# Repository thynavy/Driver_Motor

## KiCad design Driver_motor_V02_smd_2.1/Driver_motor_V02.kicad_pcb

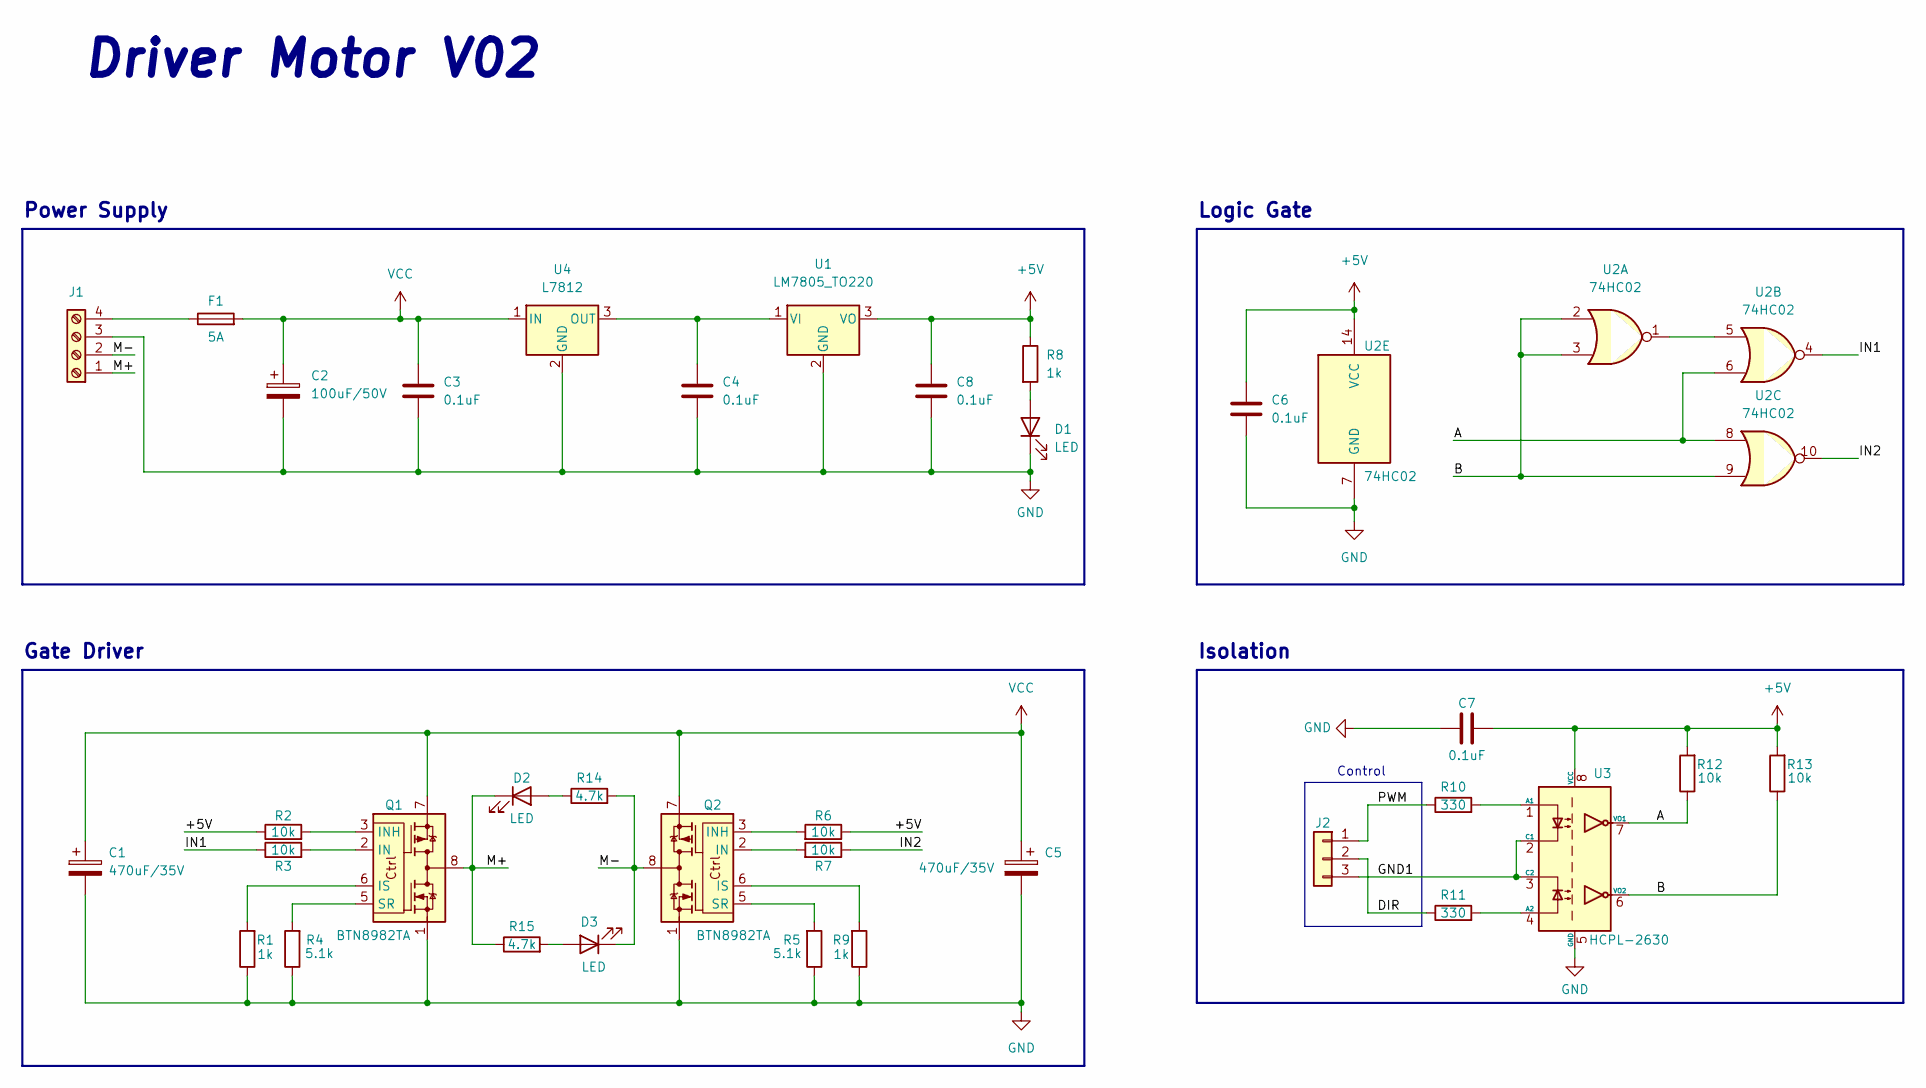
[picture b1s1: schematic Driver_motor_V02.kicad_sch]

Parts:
C1, C5: 470uF/35V; CP_Radial_D10.0mm_P5.00mm
C2: 100uF/50V; CP_Radial_D8.0mm_P3.80mm
C3, C4, C6, C7, C8: 0.1uF; C_0805_2012Metric
D1, D2, D3: LED; LED_0805_2012Metric
F1: 5A; Fuseholder_Cylinder-5x20mm_Schurter_0031_8201_Horizontal_Op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
J1: Screw_Terminal_01x04; KF7.62_2O
J2: Conn_01x03; JST_XH_B3B-XH-A_1x03_P2.50mm_Vertical
Q1, Q2: BTN8982TA; TO-263-7_TabPin8
R1, R8, R9: 1k; R_0805_2012Metric
R2, R3, R6, R7, R12, R13: 10k; R_0805_2012Metric
R4, R5: 5.1k; R_0805_2012Metric
R10, R11: 330; R_0805_2012Metric
R14, R15: 4.7k; R_0805_2012Metric
U1: LM7805_TO220; TO-252-2
U2: 74HC02; DIP-14_W7.62mm_Socket_LongPads
U3: HCPL-2630; DIP-8_W7.62mm_Socket_LongPads
U4: L7812; TO-252-2

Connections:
+5V: C6.1, C7.2, C8.1, R2.1, R6.1, R8.1, R12.2, R13.2, U1.3 (VO), U2.14 (VCC), U3.8 (VCC)
/A: R12.1, U2.6, U2.8, U3.7 (VO1)
/B: R13.1, U2.2, U2.3, U2.9, U3.6 (VO2)
/DIR: J2.2, R11.1
/GND1: J2.3, U3.2 (C1), U3.3 (C2)
/IN1: R3.1, U2.4
/IN2: R7.1, U2.10
/M+: D2.1 (K), J1.1, Q1.4, Q1.8, R15.1
/M-: D3.1 (K), J1.2, Q2.4, Q2.8, R14.2
/PWM: J2.1, R10.1
GND: C1.2, C2.2, C3.2, C4.2, C5.2, C6.2, C7.1, C8.2, D1.1 (K), J1.3, Q1.1, Q2.1, R1.1, R4.1, R5.1, R9.1, U1.2 (GND), U2.7 (GND), U3.5 (GND), U4.2 (GND)
unnamed: C4.1, U1.1 (VI), U4.3 (OUT)
unnamed: D1.2 (A), R8.2
unnamed: D2.2 (A), R14.1
unnamed: D3.2 (A), R15.2
unnamed: F1.1, J1.4
unnamed: Q1.2 (IN), R3.2
unnamed: Q1.3 (INH), R2.2
unnamed: Q1.5 (SR), R4.2
unnamed: Q1.6 (IS), R1.2
unnamed: Q2.2 (IN), R7.2
unnamed: Q2.3 (INH), R6.2
unnamed: Q2.5 (SR), R5.2
unnamed: Q2.6 (IS), R9.2
unnamed: R10.2, U3.1 (A1)
unnamed: R11.2, U3.4 (A2)
unnamed: U2.1, U2.5
VCC: C1.1, C2.1, C3.1, C5.1, F1.2, Q1.7, Q2.7, U4.1 (IN)

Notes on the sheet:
Driver Motor V02
Power Supply
Control
Gate Driver
Isolation
Logic Gate

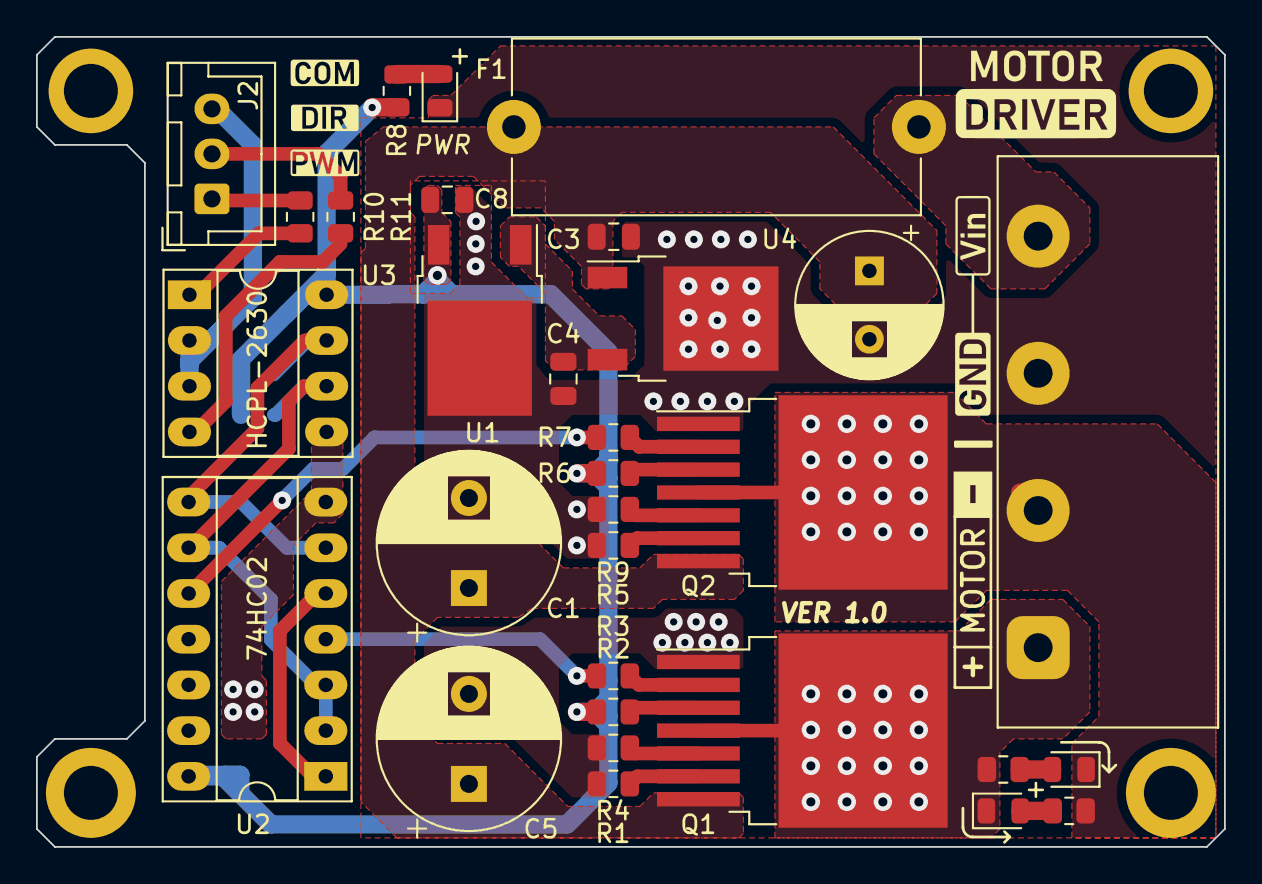
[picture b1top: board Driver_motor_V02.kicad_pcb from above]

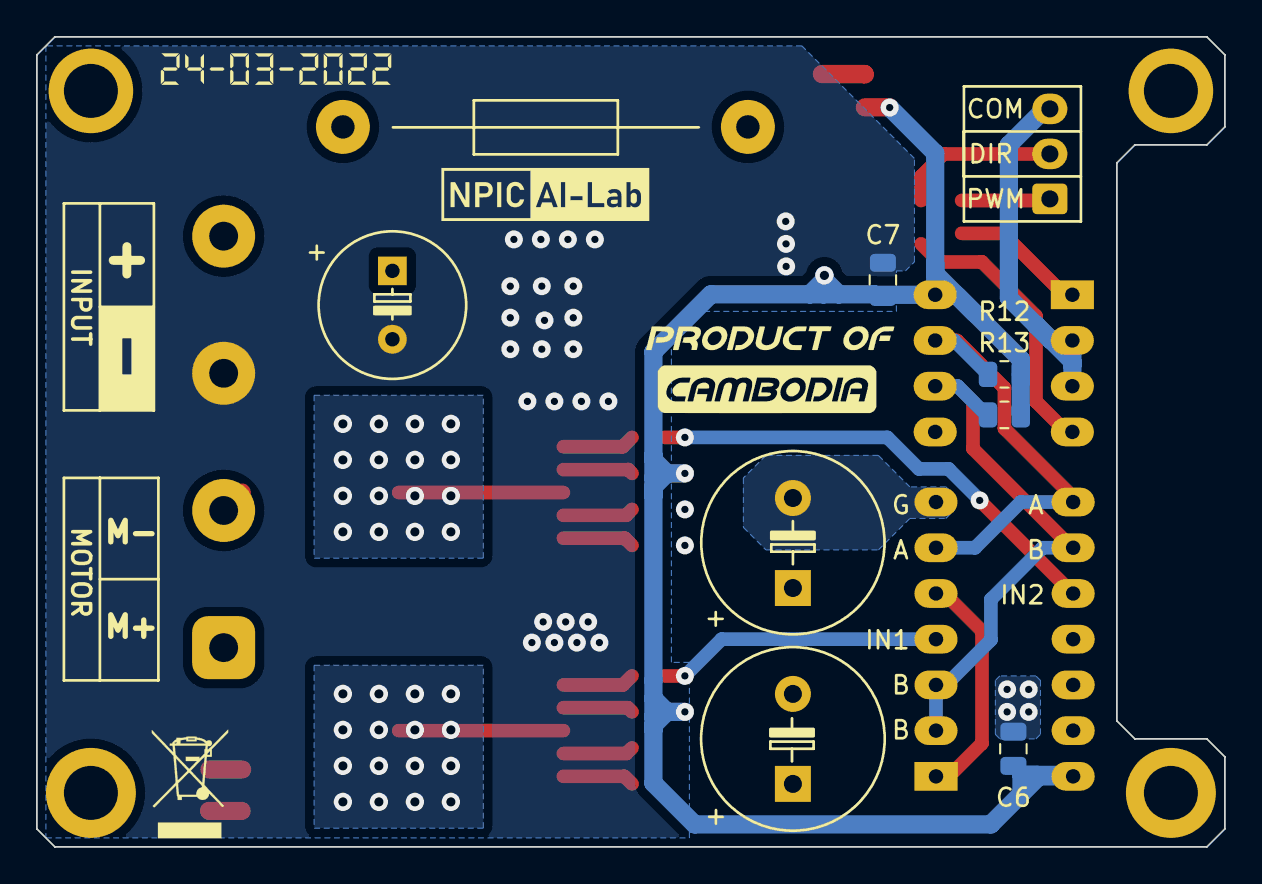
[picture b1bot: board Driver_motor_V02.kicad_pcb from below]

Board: 2 copper layers, 66.0 x 45.0 mm, 35 parts (4 on the bottom side), 28 nets.

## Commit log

2024-11-12 New File Upload
